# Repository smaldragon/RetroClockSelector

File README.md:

# Retro Clock Selector

This is a very simple universal mod board for retro systems, that selects between one of two clocks sources, for example, to select between PAL and NTSC clocks.

This board uses only a single 74-series IC (74HCT00) and generic through-hole passive components.

> This is a generic board, **there are no instructions nor warranty provided**, ideal component values and installation will vary depending on the particular system this board is installed in, **please carefully read the schematics for both this board and your system, and analyze how this pertains to your use case**.

## Theory of Operation

This board connects to a system through 4 wires: Power (Vcc), Ground (Gnd), Clock Output (Out) and Clock Select (Sel).

The Sel wire selects which of the two **pierce oscilator circuits** (Hi or Lo) is currently active, and is typically driven by the switch on the modboard. On many sega systems, for example, the Hi oscillator would be NTSC and Lo would be PAL.

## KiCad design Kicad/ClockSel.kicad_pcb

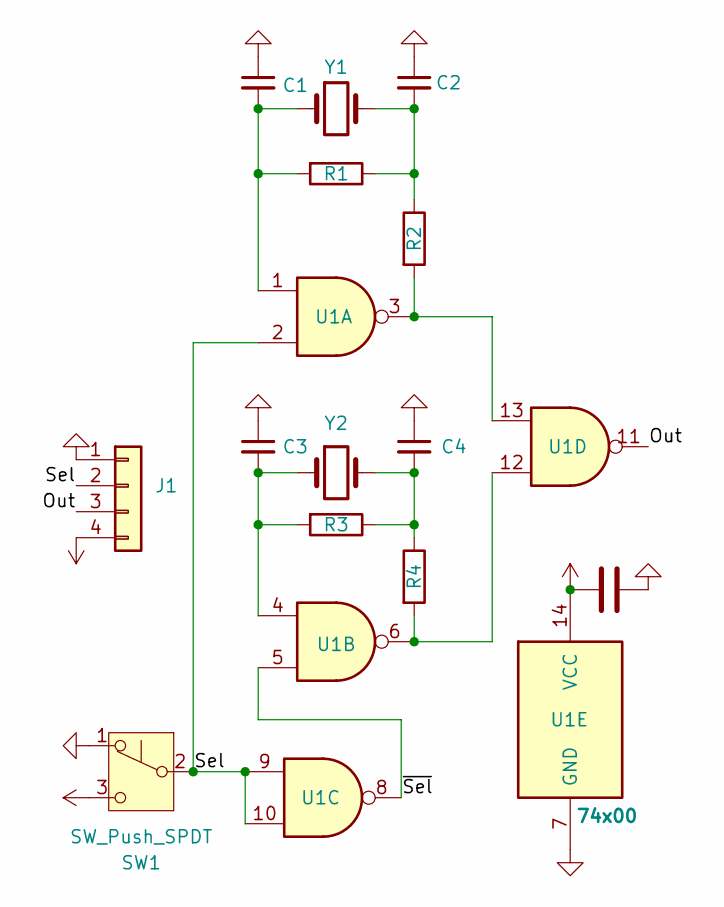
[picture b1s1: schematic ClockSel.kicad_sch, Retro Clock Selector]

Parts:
C1, C2, C3, C4: C_Small; C_Disc_D3.0mm_W1.6mm_P2.50mm
C5: 100nF; C_Disc_D3.0mm_W1.6mm_P2.50mm
J1: Conn_01x04; PinHeader_1x04_P2.54mm_Vertical
R1, R2, R3, R4: R; R_Axial_DIN0204_L3.6mm_D1.6mm_P2.54mm_Vertical
SW1: SW_Push_SPDT; SW_Slide_SPDT_Straight_CK_OS102011MS2Q
U1: 74x00; DIP-14_W7.62mm
Y1, Y2: Crystal; Crystal_HC49-U_Vertical

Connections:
/Out: J1.3, U1.11
/Sel: J1.2, SW1.2 (B), U1.2, U1.9, U1.10
/~Sel: U1.5, U1.8
GND: C1.1, C2.1, C3.1, C4.1, C5.2, J1.1, SW1.1 (A), U1.7 (GND)
unnamed: C1.2, R1.2, U1.1, Y1.1
unnamed: C2.2, R1.1, R2.1, Y1.2
unnamed: C3.2, R3.2, U1.4, Y2.1
unnamed: C4.2, R3.1, R4.1, Y2.2
unnamed: R2.2, U1.3, U1.13
unnamed: R4.2, U1.6, U1.12
VCC: C5.1, J1.4, SW1.3 (C), U1.14 (VCC)

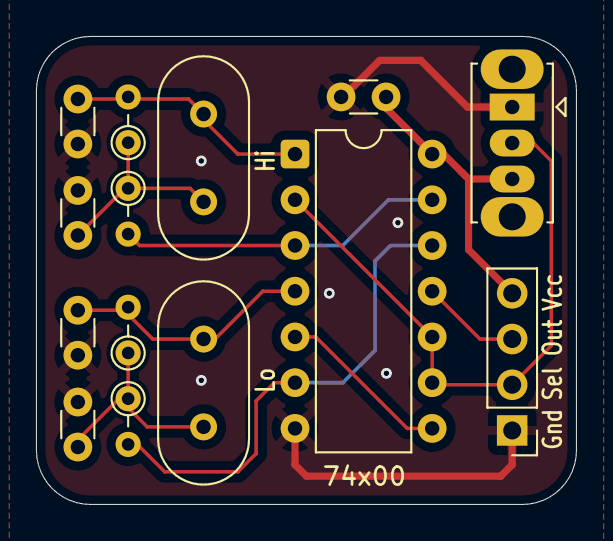
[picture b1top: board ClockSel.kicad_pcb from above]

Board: 2 copper layers, 30.0 x 26.0 mm, 14 parts (0 on the bottom side), 11 nets.
